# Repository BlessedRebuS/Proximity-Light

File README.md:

# Proximity-Light

Sensor Light powered by a ultrasound module (HC-SR04) built on a chip. (SMD version). 
When the proximity sensor sees an obsacle (for example your hand) the relays are toggled **(ON-OFF)** / **(OFF-OF)** and the 12v powers the pins.
The button triggers an interrupt (ATMega328P comes with D2 and D3 digital pin that can be used as interrupts, in this project only the D3 is used) that cycles 3 states:

* Relay 1 ON Relay 2 OFF
* Relay 1 ON Relay 2 ON
* Relay 1 OFF Relay 2 OFF

The project idea is to put two led strips in the pair of pins near the supply that can help you illuminate the kitchen/bathroom/other rooms. Leds can be replaced with all type of stuff you want but it hasn't to drain much current (Max around 0.1 amp), you have only to solder your device in place. Now are only supported devices without data pins, so you have to use only the **VCC** and **GND**.

[See polarity and button](https://github.com/BlessedRebuS/Proximity-Light/blob/main/images/PinButton.png)

# Board

## Electronic Board
Created with Autodesk EAGLE and Fusion360 Electronic.

To connect all pins we simply used autorouting.

## Board Schematic - Libraries
You can find all the libraries *(Footprint, Symbols and 3DModels)* [Here](https://github.com/BlessedRebuS/Proximity-Light/tree/main/libraries/Footprints)

## 3D Model

Designed and rendered in Fusion360

# Components

* ATMega328P  [Read more](#about-the-atmega328p)
* 22 PF Capacitors (Not polarized) 2x
* 20 MHZ Quartz Oscillator
* 220-1k OHM Resistor
* Ultrasonic Sensor (HC-SR04)
* 12 to 5V DC Mosfet
* 12V Supply Holder
* 12v Relays x2
* Button
* 2x1 pins x2
* 2x3 pins

# About the ATMega328P

ATMega328p is a very versatile processor, mounted on Arduino, that can be used also separately with a different pinout. In this case the base clock 8MHZ is replaced with the 16MHZ clock (not necessary) connected to the two grounded capacitors to generate the oscillation.

**How to program it?** I suggest to use the [USBASP programmer](www.learningaboutelectronics.com/Articles/Program-AVR-chip-using-a-USBASP-with-10-pin-cable.php) (6 or 10 PIN), but you can use an Arduino using "Arduino as ISP" programming.

## The clock
As [Here](https://doc.riot-os.org/group__boards__atmega328p.html) is explained:

> The ATmega328p has two internal oscillators clocked at 8MHz and at 128kHz that allow it to be operated without any external clock source or crystal. By default the fuses are configured to use the internal 8MHz oscillator and a clock divider resulting in a clock speed of 1MHz. By clearing the CKDIV8 fuse the clock divider can be disabled to operate the ATmega328p at 8MHz without an external clock source. This can be done like this:
> 
> `avrdude -c usbtiny -p m328p -B 32 -U lfuse:w:0xe2:m`
> 
> (Replace usbtiny with the ISP programmer you are using. The -B 32 might be needed on some ISP programmers to communicate with slow ATmega MCUs. It will not be needed anymore after the clock device has been disabled.)
This "board" is configured to use 8MHz as core clock, so that the ATmega328p runs at the highest frequency possible without external clock sources.
By setting the environment variable ATMEGA328P_CLOCK to a custom frequency in Hz (e.g. 1000000 for 1MHz), this core clock can be changed easily. Refer to the datasheet on how to configure the ATmega328p to use an external crystal, an external clock source or the clock divider.
<p align="right">

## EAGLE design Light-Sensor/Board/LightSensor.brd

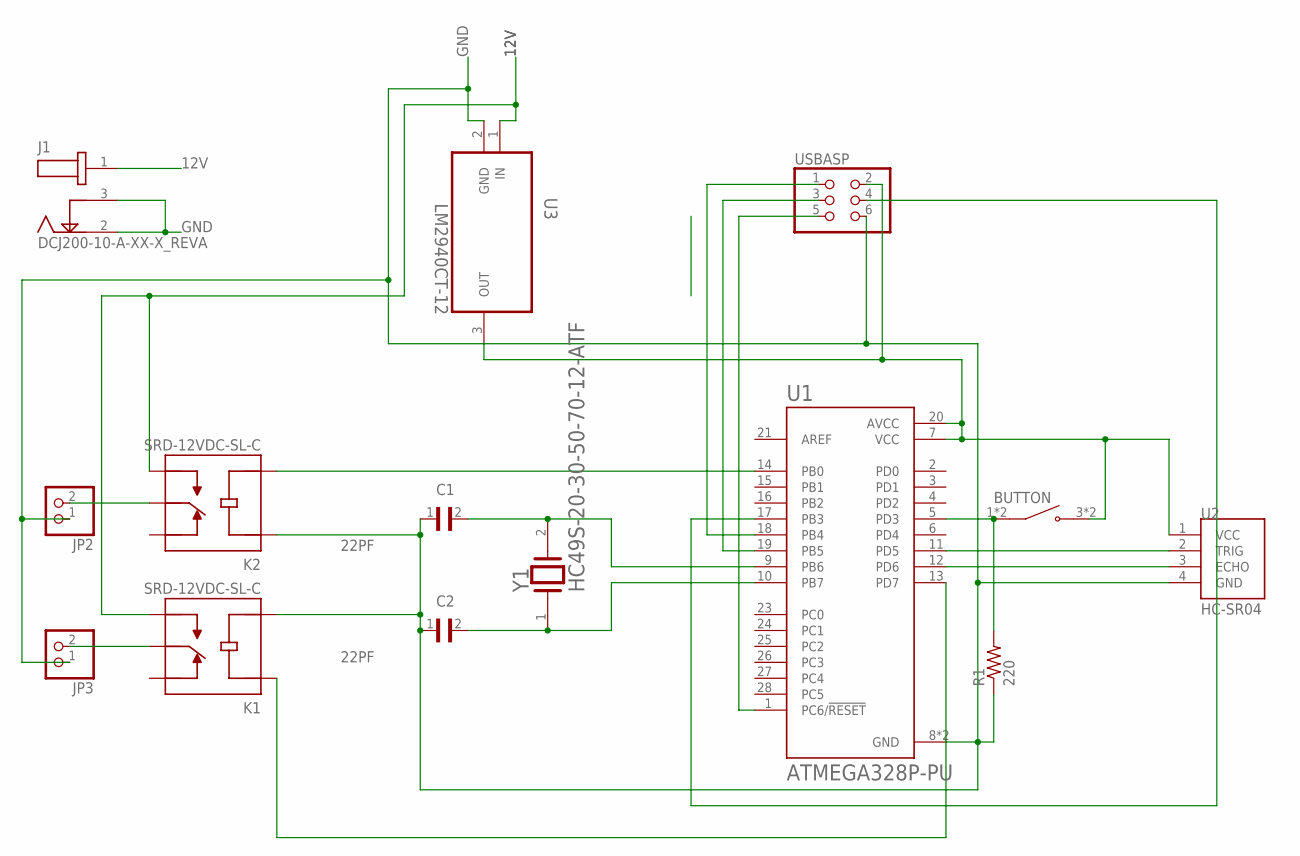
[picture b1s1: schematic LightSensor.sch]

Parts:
C1, C2: 22PF; CAP_DE21XSA220KN3AX02F
J1: DCJ200-10-A-XX-X_REVA; GCT_DCJ200-10-A-XX-X_REVA
JP2, JP3: PINHD-1X2; 1X02
K1, K2: SRD-12VDC-SL-C; RELAY_SRD-12VDC-SL-C
R1: 220; 0309/12
S1: BUTTON
U1: ATMEGA328P-PU; DIP794W46P254L2967H457Q28B
U2: HC-SR04; XCVR_HC-SR04
U3: LM2940CT-12; TO254P470X1016X2222-3P
USBASP: PINHD-2X3; 2X03
Y1: 20MHZ; MULTICOMP_HC49S-20-30-50-70-12-ATF_0

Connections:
12V: J1.1, K1.NO, K2.NO, U3.1 (IN)
BUTTON: R1.2, S1.1 (COM), S1.2 (COM), U1.5 (PD3)
GND: C1.1, C2.1, J1.2, J1.3, JP2.1, JP3.1, K1.COIL2, K2.COIL1, R1.1, U1.8 (GND), U1.22 (GND), U2.4 (GND), U3.2 (GND), USBASP.6
unnamed: U1.17 (PB3), USBASP.4
unnamed: U1.1 (PC6/!RESET), USBASP.5
unnamed: U1.19 (PB5), USBASP.3
unnamed: U1.18 (PB4), USBASP.1
unnamed: C1.2, U1.9 (PB6), Y1.2
unnamed: C2.2, U1.10 (PB7), Y1.1
unnamed: U1.11 (PD5), U2.2 (TRIG)
unnamed: U1.12 (PD6), U2.3 (ECHO)
unnamed: K1.COIL1, U1.13 (PD7)
unnamed: K2.COIL2, U1.14 (PB0)
unnamed: JP2.2, K2.COM
unnamed: JP3.2, K1.COM
unnamed: S1.3 (NO), S1.4 (NO), U1.7 (VCC), U1.20 (AVCC), U2.1 (VCC), U3.3 (OUT), USBASP.2

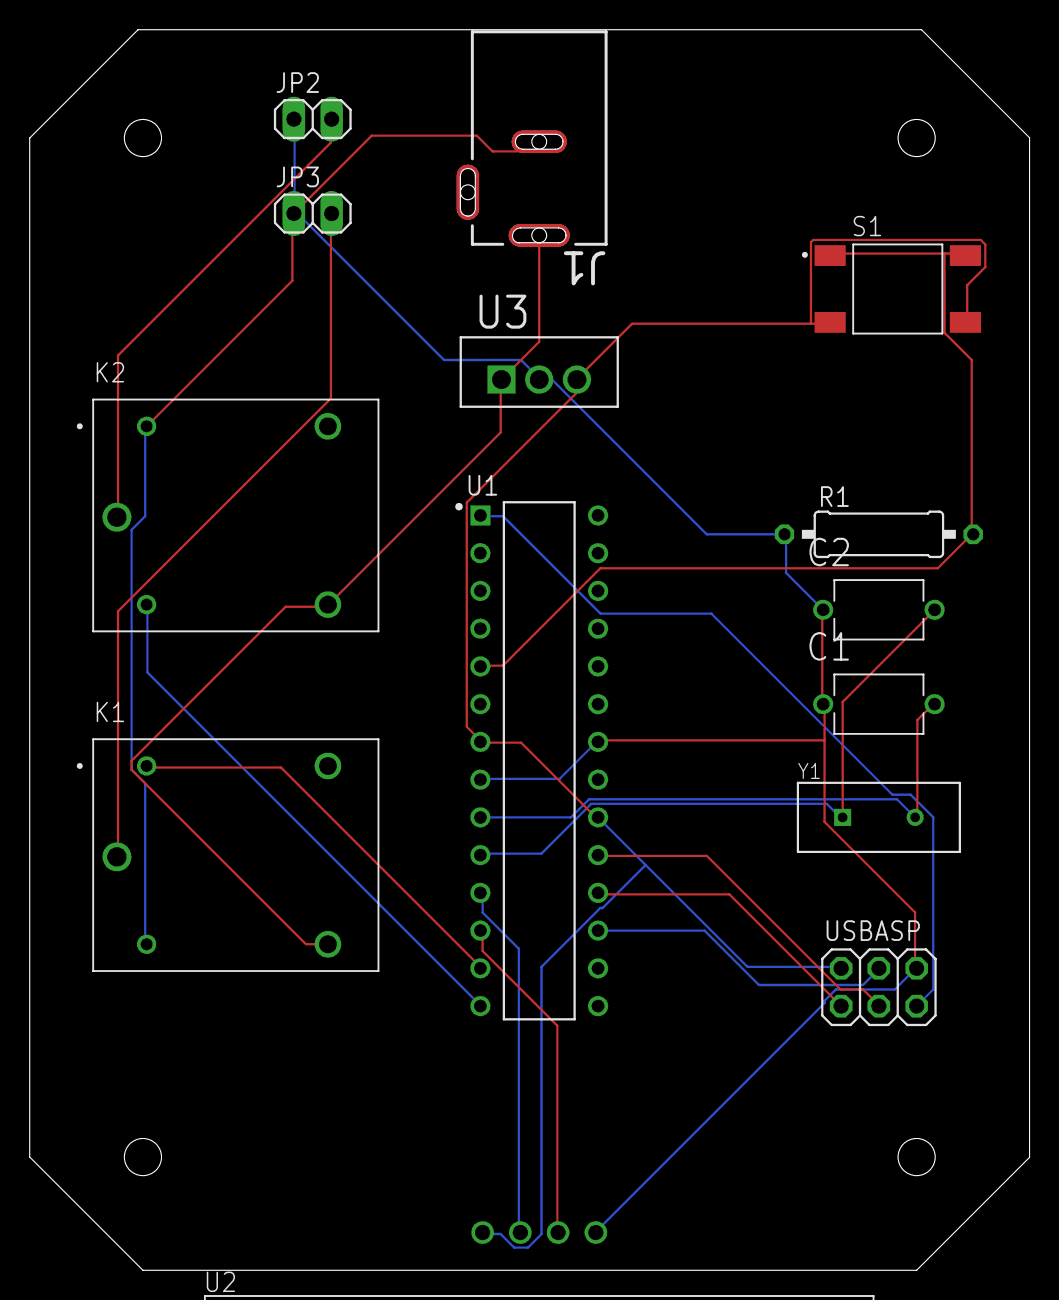
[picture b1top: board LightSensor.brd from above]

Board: 2 copper layers, 67.3 x 83.5 mm, 14 parts (0 on the bottom side), 16 nets.

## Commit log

2021-09-14 File caricati
2021-11-24 New Code
2021-11-24 Visual Studio Code project
    Added visual studio code project, requires PlatformIO
2021-11-25 Update main.cpp
    Added DEBUG_MODE
2021-11-25 Lights
    Added FastLED light support
2021-11-26 Fix Code
